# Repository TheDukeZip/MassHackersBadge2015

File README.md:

# MassHackersBadge2015

## Programming

The stock firmware is written in the Arduino IDE. Before making modifications, you should make sure you can properly flash the stock code before going wild. You will need:

* Arduino IDE (Recommend 1.6.5)
* <a href="https://www.pjrc.com/teensy/td_download.html">Teensyduino</a> plugin for Arduino

During the Teensyduino plugin, it will ask you any additional libraries you wish to install. **You must minimally install the SoftPWM library**, which is a pulse width modulation library which allows the badge to fade the LEDs in and out instead of just turn them on and off.

When flashing the Teensy module, use the following settings found under the Arduino menu *Tools*

* Board: "Teensy 2.0"
* CPU Speed: "8 MHz"

It is **VERY IMPORTANT** to set the speed to *8 MHz* or lower. Your teensy board is modified to operate at 3.3 volts instead of the default 5 volts. **Running at the default 16MHz is OVERCLOCKING** the processor, which will probably work fine for a while, but I can't guarantee how long it will last in the desert heat. Don't freak out if you do it by accident and the LEDs flash extra fast, just reflash again with the correct clock speed.

The Arduino IDE will then prompt you to press the reset button on the Teensy module, after which it will flash the board. You must press the reset button, since access to the bootloader through USB is disabled in the badge firmware to save power.

The Teensy module can be removed from the badge, and is populated with headers so you can pop it into a breadboard and use it for any other project you desire. Remember it has been modified to run at 3.3 volts, if you need to switch it back to 5 volts for other uses, <a href="https://www.pjrc.com/teensy/3volt.html">follow the instructions here at the part "If you decide to switch back to 5 volts..."</a>

## Firmware

### Adding a new color into the rotation
* Insert color into the `LED_COLOR` enum of the header file, ideally somewhere before `LED_COLOR_WHITE`
* Insert the RGB color values into the main file, `LEDColorMap` in the order it was inserted into `LED_COLOR` You will also need to increase the array size to accomodate this

That's it! The color automatically gets inserted into the rotation upon flashing. There is a trick to the SoftPWM library. Let's say for example you create a color that is RED 127, GREEN 255, BLUE 0. And your fade in time is 1000ms. The red and green fade in at the same rate, so red reaches its full brightness after 500ms, but green continues to fade in for an additional 500ms. You can overcome this by individually setting the fade in/out component of the red portion of the LED to be double that of the green portion of the LED. I started some work on this in the function `offLEDCorrected()` but it is up to you to finish it, and write a complementary function for turning on the LEDs!

### Adding a new mode into the rotation
* Insert the mode into the `LED_MODE` enum of the header file, which *must* be before `LED_MODE_END`
* Set the LED fade in and fade out times for your mode in `LEDModeFadeTimes` in the main file. You will also need to change the size of the array to accomodate this
* Create a handler function that does whatever you want to the LEDs - See other modes for examples
* Add a call to your handler function in the main `loop()` case statement: `switch(currentMode)`

The button presses are not interrupt based, you should plan to call the function `checkButton()` at least after every 50ms during your mode. (This is not truely a 50ms delay due to running at 8MHz, it is closer to 100ms)

## Hardware

Schematic and PCB was designed in Eagle 6.6.0. Eagle does not pre-load the ground pours when loading the PCB design. After opening the PCB you should run the "rats nest" tool to populate the ground pours.

You can remove the Teensy 2.0 module from the badge and put it into a breadboard for other fun hardware projects. The Teensy board is modified to operate at 3.3 volts, if you need to switch it back to 5 volts for other uses, <a href="https://www.pjrc.com/teensy/3volt.html">follow the instructions here at the part "If you decide to switch back to 5 volts..."</a>

### Errata

* Resistors for RED LEDs are R13 through R18 and should be 150 ohms
* Resistors for GREEN and BLUE LEDs are R1 through R12 and should be 15 ohms
* For the RGB LEDs in the BOM, the LED should be soldered on the board with the pin 1 marker on the bottom left, not the top right as on the silk screen

### BOM
| Qty | Description | MPN | Digikey PN |
|-----|-------------|-----|------------|
| 1   | Teensy 2.0  | -   |  - |
| 6   | RGB LED     | CLVBA-FKA-CAEDH8BBB7A363 | CLVBA-FKA-CAEDH8BBB7A363CT-ND |
| 6   | 150 ohm 0603 resistor | RMCF0603FT150R | RMCF0603FT150RCT-ND |
| 12  | 15 ohm 0603 resistor  | RMCF0603FT15R0 | RMCF0603FT15R0CT-ND | 
| 1 | Voltage regulator for Teensy | MCP1825S-3302E/DB | MCP1825S-3302E/DB-ND |
| 2 | Header for Teensy board | PREC012SAAN-RC | S1012EC-12-ND |
| 2 | Socket for badge PCB | 929974-01-12-RK | 929974E-01-12-ND |
| 1 | CR123A Battery Holder | 1019 | 36-1019-ND |
| 1 | Momentary Switch | KMR231NG LFS | CKN10246CT-ND |

### Files

Eagle Project: **Hardware/MassHackersBadge2015.pro**<br>
Eagle Schematic: **Hardware/MassHackersBadge2015.sch**<br>
Eagle PCB: **Hardware/MassHackersBadge2015.brd**

Gerbers for manufacturing: **Hardware/Gerbers**

Design rule check and CAM file for Gerber generation for DirtyPCBs: **Hardware/DirtyPCBs**

### Available Hardware Pins

There are <a href="https://www.pjrc.com/teensy/pinout.html">3 pins</a> available on the Teensy 2.0 to add additional hardware:
* Pin 9 - Digital I/O
* Pin 10 - Digital I/O
* Pin 11 - Analog or Digital I/O

You will need to remove pins you use from the array `UnusedPins` so they do not get disabled during the power conservation routine

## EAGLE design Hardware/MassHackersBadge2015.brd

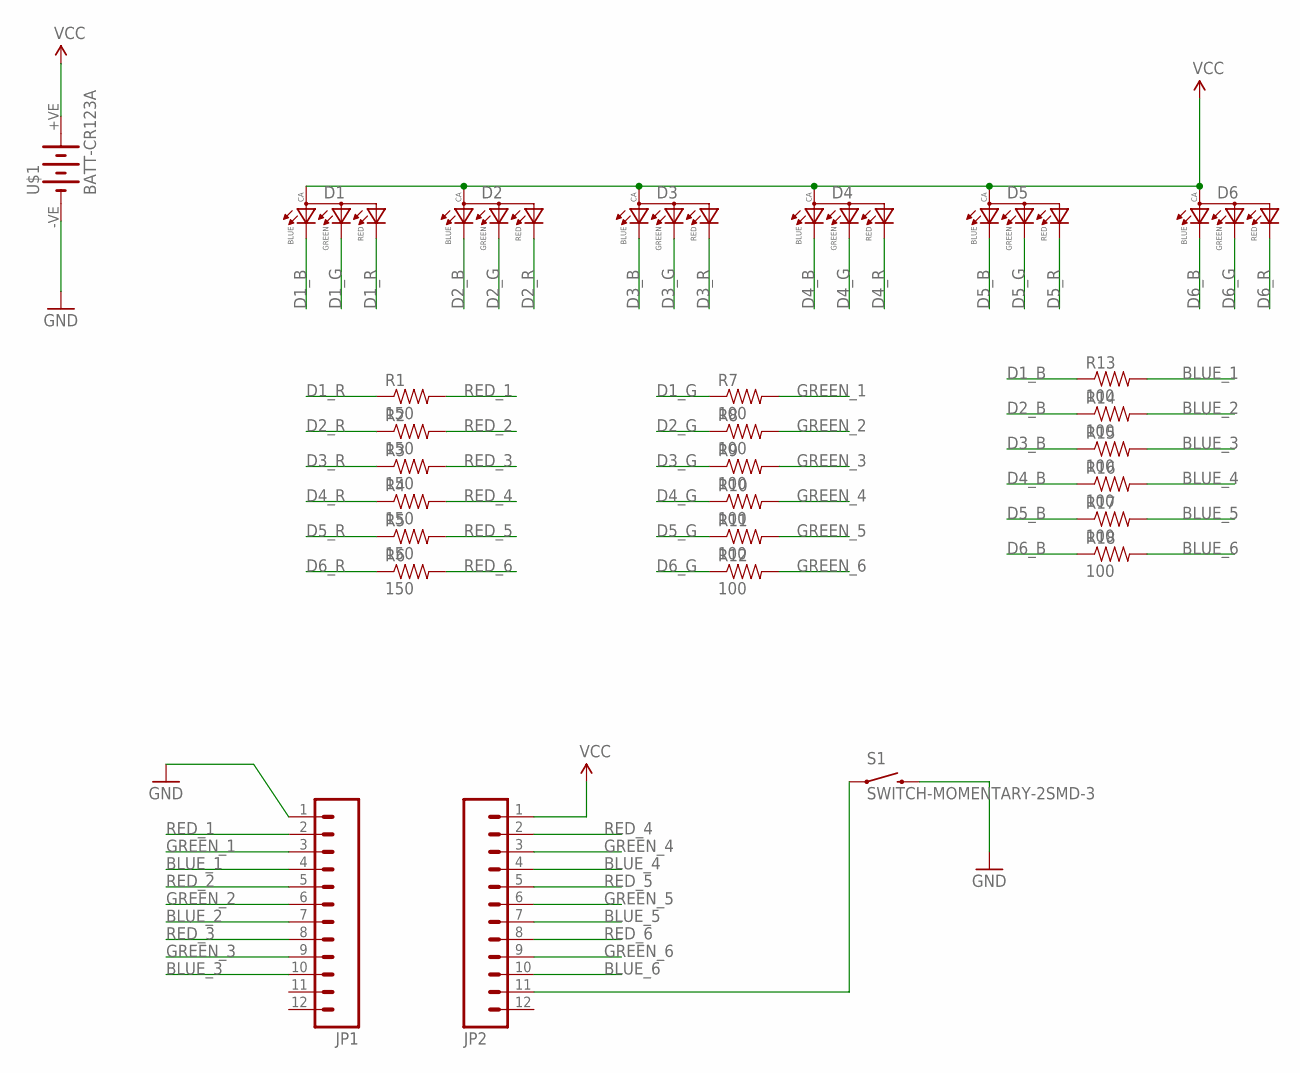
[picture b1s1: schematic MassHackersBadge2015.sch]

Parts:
D1, D2, D3, D4, D5, D6: 0.13_RGB_LEDPLCC; P-LCC-4-3
JP1, JP2: M12PTH; 1X12
R1, R2, R3, R4, R5, R6: 150; 0603-RES
R7, R8, R9, R10, R11, R12, R13, R14, R15, R16, R17, R18: 100; 0603-RES
S1: SWITCH-MOMENTARY-2SMD-3; TACTILE_SWITCH_SMD-3
U$1: BATT-CR123A; KEYSTONE-2/3A

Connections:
BLUE_1: JP1.4, R13.2
BLUE_2: JP1.7, R14.2
BLUE_3: JP1.10, R15.2
BLUE_4: JP2.4, R16.2
BLUE_5: JP2.7, R17.2
BLUE_6: JP2.10, R18.2
D1_B: D1.3 (BLUE), R13.1
D1_G: D1.2 (GREEN), R7.1
D1_R: D1.1 (RED), R1.1
D2_B: D2.3 (BLUE), R14.1
D2_G: D2.2 (GREEN), R8.1
D2_R: D2.1 (RED), R2.1
D3_B: D3.3 (BLUE), R15.1
D3_G: D3.2 (GREEN), R9.1
D3_R: D3.1 (RED), R3.1
D4_B: D4.3 (BLUE), R16.1
D4_G: D4.2 (GREEN), R10.1
D4_R: D4.1 (RED), R4.1
D5_B: D5.3 (BLUE), R17.1
D5_G: D5.2 (GREEN), R11.1
D5_R: D5.1 (RED), R5.1
D6_B: D6.3 (BLUE), R18.1
D6_G: D6.2 (GREEN), R12.1
D6_R: D6.1 (RED), R6.1
GND: JP1.1, S1.4 (2), U$1.-VE (-)
GREEN_1: JP1.3, R7.2
GREEN_2: JP1.6, R8.2
GREEN_3: JP1.9, R9.2
GREEN_4: JP2.3, R10.2
GREEN_5: JP2.6, R11.2
GREEN_6: JP2.9, R12.2
unnamed: JP2.11, S1.1
RED_1: JP1.2, R1.2
RED_2: JP1.5, R2.2
RED_3: JP1.8, R3.2
RED_4: JP2.2, R4.2
RED_5: JP2.5, R5.2
RED_6: JP2.8, R6.2
VCC: D1.4 (ANODE), D2.4 (ANODE), D3.4 (ANODE), D4.4 (ANODE), D5.4 (ANODE), D6.4 (ANODE), JP2.1, U$1.+VE (+)

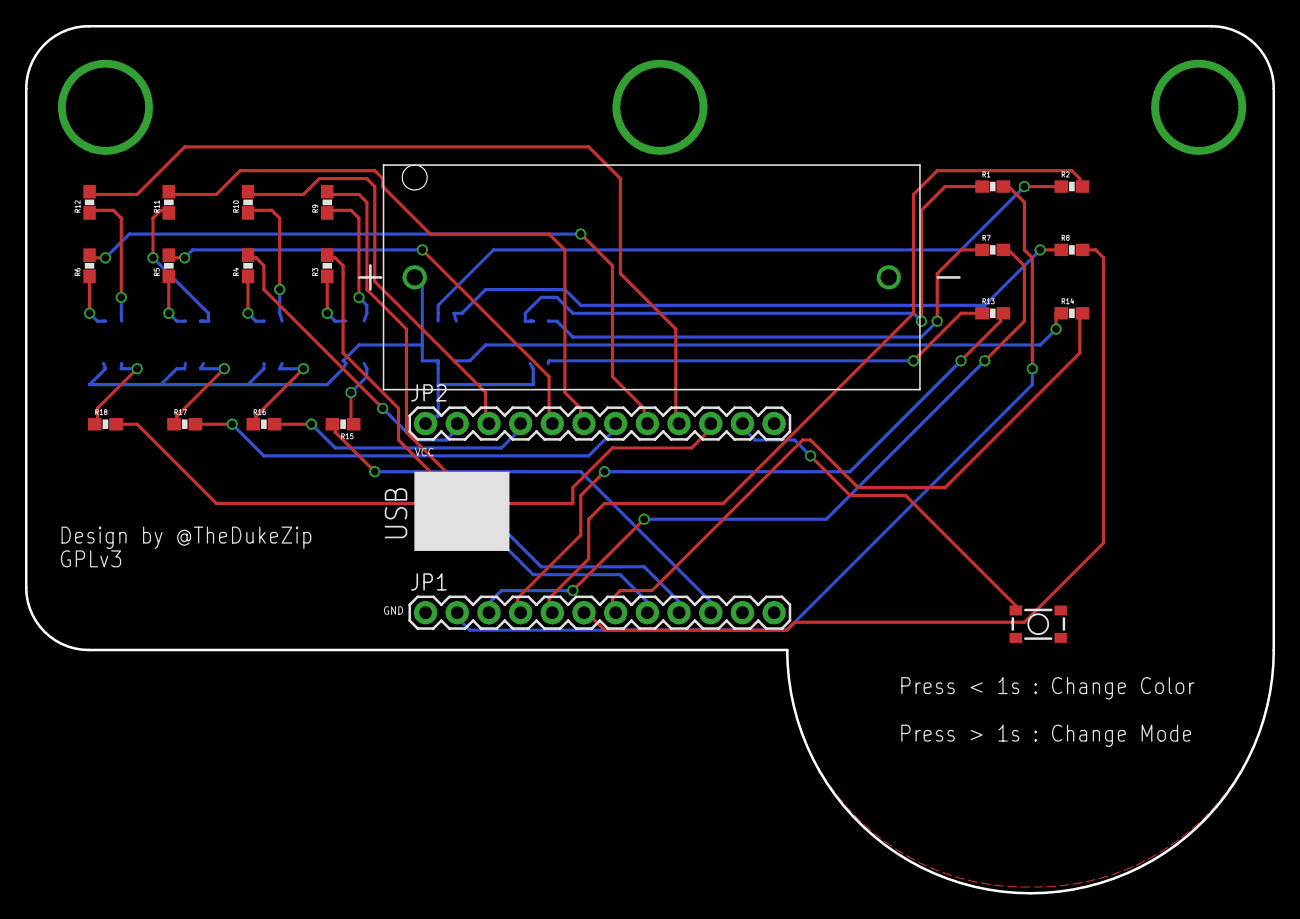
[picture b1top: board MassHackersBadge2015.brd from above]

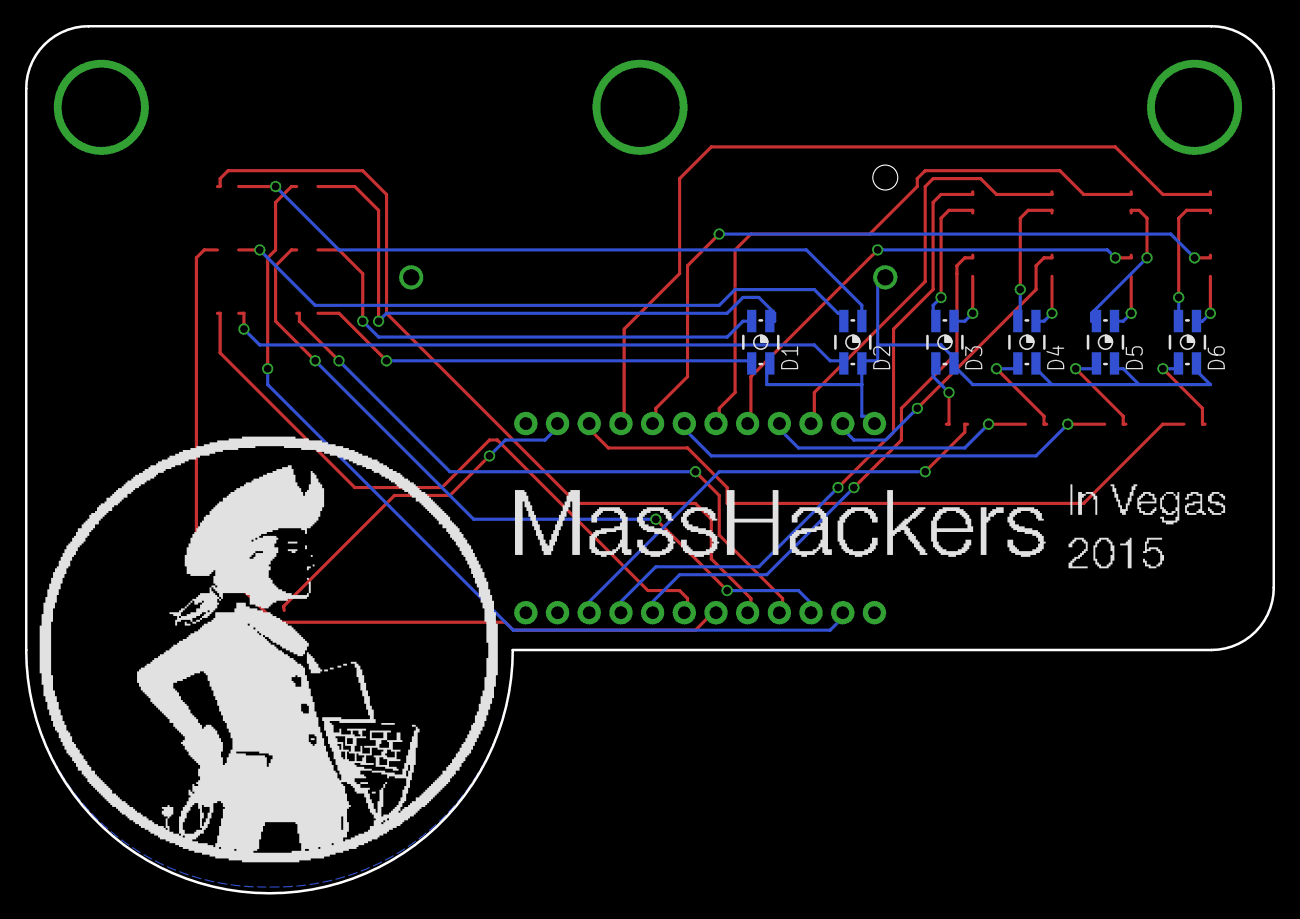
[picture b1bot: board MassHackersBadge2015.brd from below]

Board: 2 copper layers, 100.0 x 69.5 mm, 28 parts (6 on the bottom side), 39 nets.

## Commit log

2015-07-15 Preview readme
2015-08-01 Initial checkin
2015-08-01 README cleanup

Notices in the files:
Hardware/MassHackersBadge2015.brd:
GPLv3
parts and their libraries:
SparkFun-Connectors: Licensing: Creative Commons ShareAlike 4.0 International - https://creativecommons.org/licenses/by-sa/4.0
eagle-library-edeca.net-v5: This is v1 and is licensed under the Creative Commons (Attribution-Non-Commercial-Share Alike 2.0 UK)
